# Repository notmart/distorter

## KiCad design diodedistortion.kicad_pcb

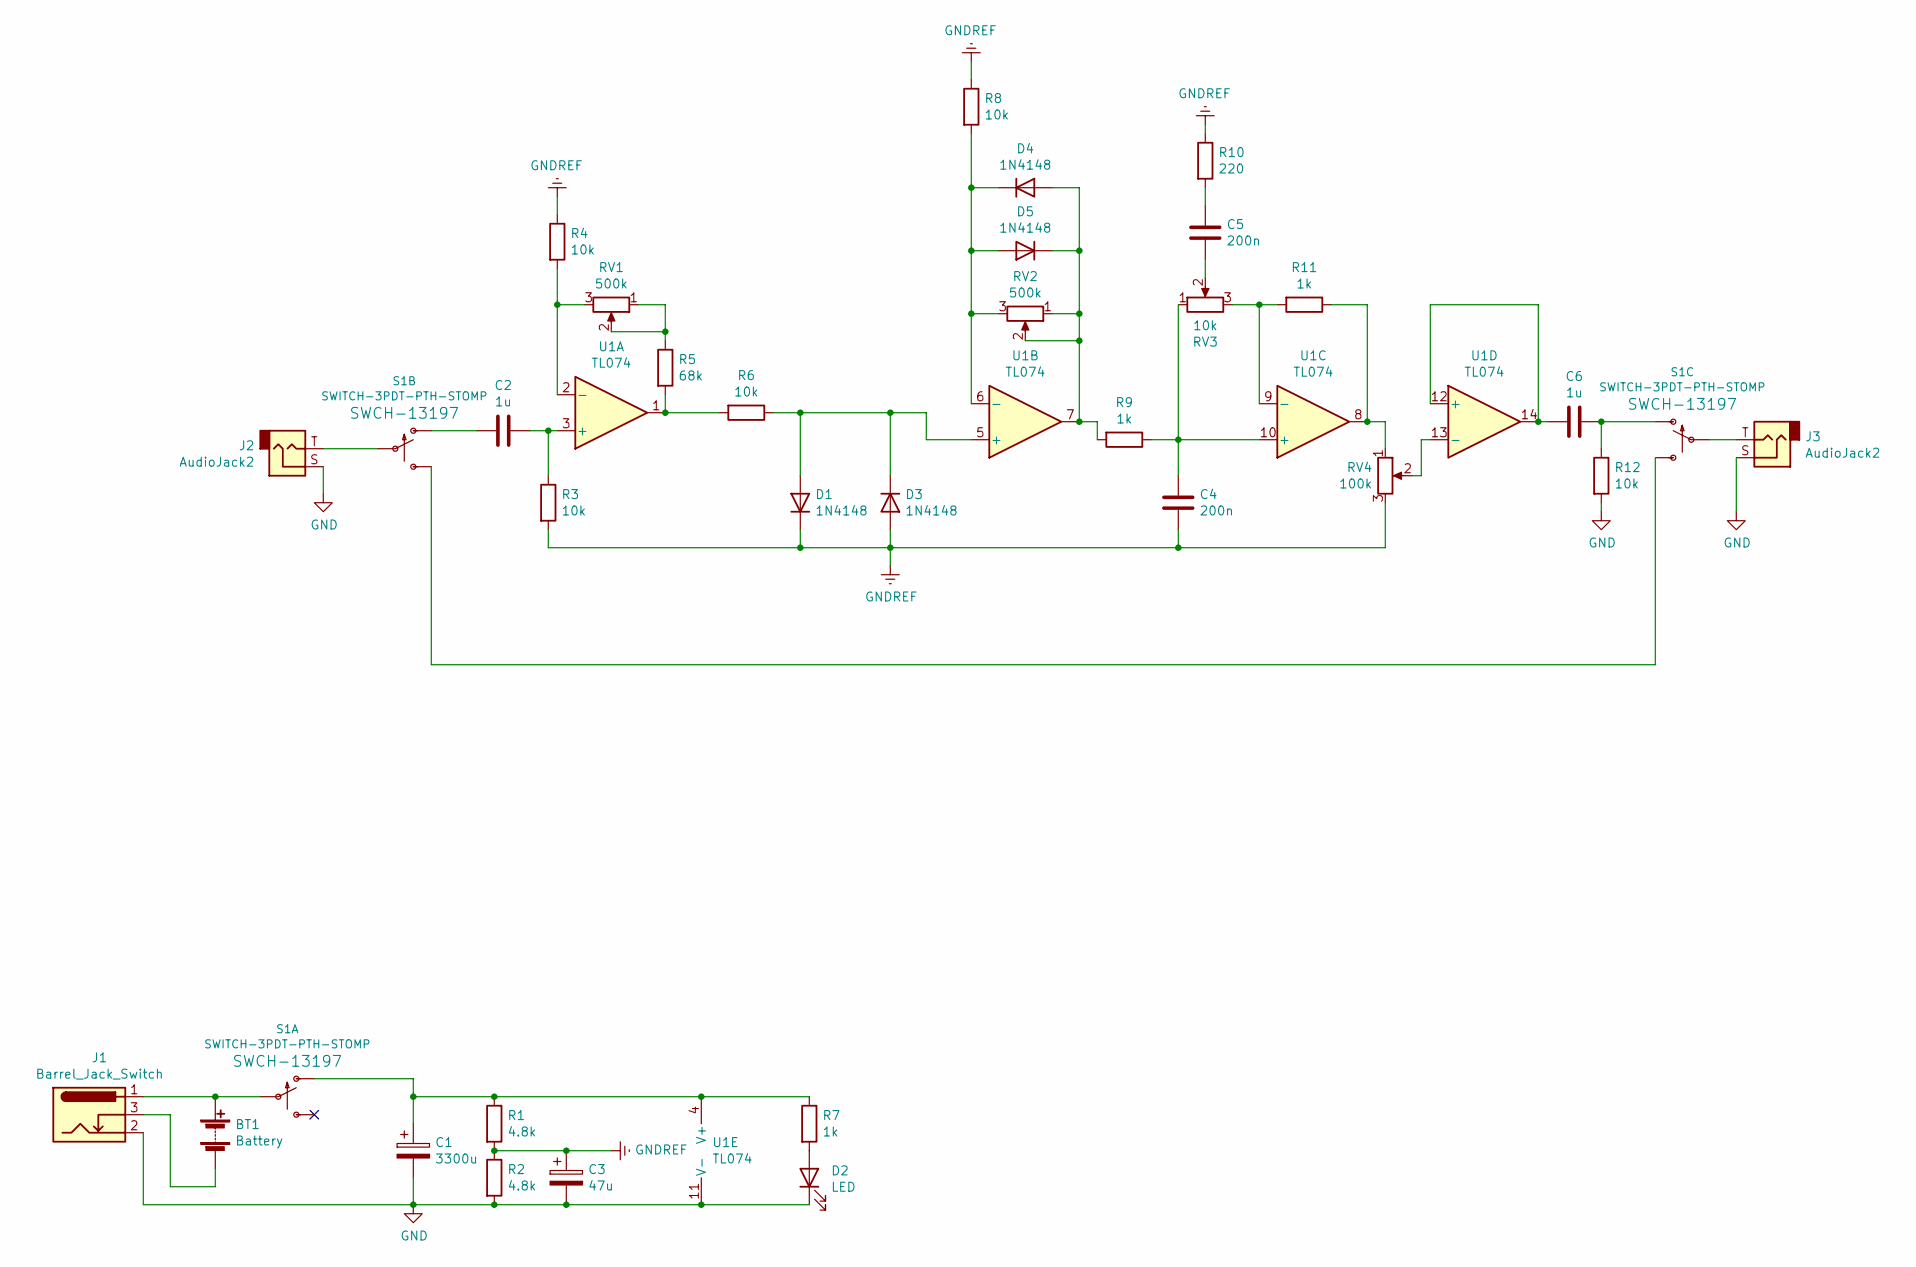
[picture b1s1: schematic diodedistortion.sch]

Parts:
BT1: Battery; 1X02
C1: 3300u; CP_Radial_D13.0mm_P5.00mm
C2, C6: 1u; C_Rect_L7.2mm_W2.5mm_P5.00mm_FKS2_FKP2_MKS2_MKP2
C3: 47u; CP_Radial_D8.0mm_P5.00mm
C4, C5: 200n; C_Rect_L7.2mm_W2.5mm_P5.00mm_FKS2_FKP2_MKS2_MKP2
D1, D3, D4, D5: 1N4148; D_DO-35_SOD27_P7.62mm_Horizontal
D2: LED; LED_D3.0mm
J1: Barrel_Jack_Switch; BarrelJack_Horizontal
J2, J3: AudioJack2; Jack 6.35mm PJ603
R1, R2: 4.8k; R_Axial_DIN0204_L3.6mm_D1.6mm_P7.62mm_Horizontal
R3, R4, R6, R8, R12: 10k; R_Axial_DIN0204_L3.6mm_D1.6mm_P7.62mm_Horizontal
R5: 68k; R_Axial_DIN0204_L3.6mm_D1.6mm_P7.62mm_Horizontal
R7, R9, R11: 1k; R_Axial_DIN0204_L3.6mm_D1.6mm_P7.62mm_Horizontal
R10: 220; R_Axial_DIN0204_L3.6mm_D1.6mm_P7.62mm_Horizontal
RV1, RV2: 500k; Potentiometer_Alps_RK09K_Single_Vertical
RV3: 10k; Potentiometer_Alps_RK09K_Single_Vertical
RV4: 100k; Potentiometer_Bourns_3386P_Vertical
S1: SWITCH-3PDT-PTH-STOMP; 3PDT_Small
U1: TL074; DIP-14_W7.62mm_Socket_LongPads

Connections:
GND: C1.2, C3.2, D2.1 (K), J1.2, J2.S, J3.S, R2.2, R12.2, U1.11 (V-)
GNDREF: C3.1, C4.2, D1.1 (K), D3.2 (A), R1.2, R2.1, R3.2, R4.1, R8.1, R10.1, RV4.3
unnamed: BT1.1 (+), J1.1, S1.P$2
unnamed: BT1.2 (-), J1.3
unnamed: C1.1, R1.1, R7.1, S1.P$1 (O), U1.4 (V+)
unnamed: C2.1, R3.1, U1.3 (+)
unnamed: C2.2, S1.P$4 (O)
unnamed: C4.1, R9.1, RV3.1, U1.10 (+)
unnamed: C5.1, R10.2
unnamed: C5.2, RV3.2
unnamed: C6.1, R12.1, S1.P$7 (O)
unnamed: C6.2, U1.12 (+), U1.14
unnamed: D1.2 (A), D3.1 (K), R6.1, U1.5 (+)
unnamed: D2.2 (A), R7.2
unnamed: D4.1 (K), D5.2 (A), R8.2, RV2.3, U1.6 (-)
unnamed: D4.2 (A), D5.1 (K), R9.2, RV2.1, RV2.2, U1.7
unnamed: J2.T, S1.P$5
unnamed: J3.T, S1.P$8
unnamed: R4.2, RV1.3, U1.2 (-)
unnamed: R5.1, RV1.1, RV1.2
unnamed: R5.2, R6.2, U1.1
unnamed: R11.1, RV4.1, U1.8
unnamed: R11.2, RV3.3, U1.9 (-)
unnamed: RV4.2, U1.13 (-)
unnamed: S1.P$6 (S), S1.P$9 (S)

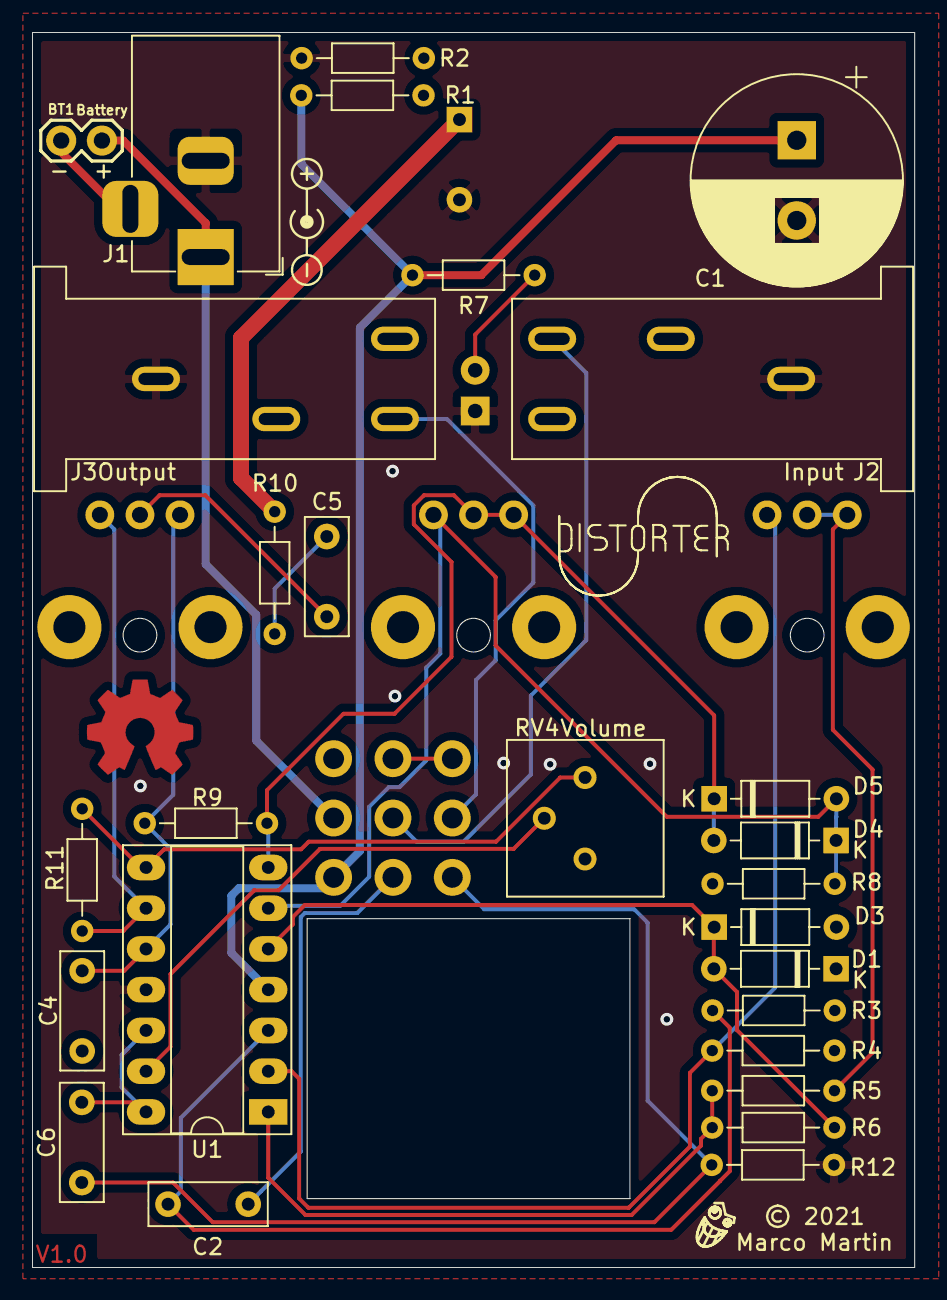
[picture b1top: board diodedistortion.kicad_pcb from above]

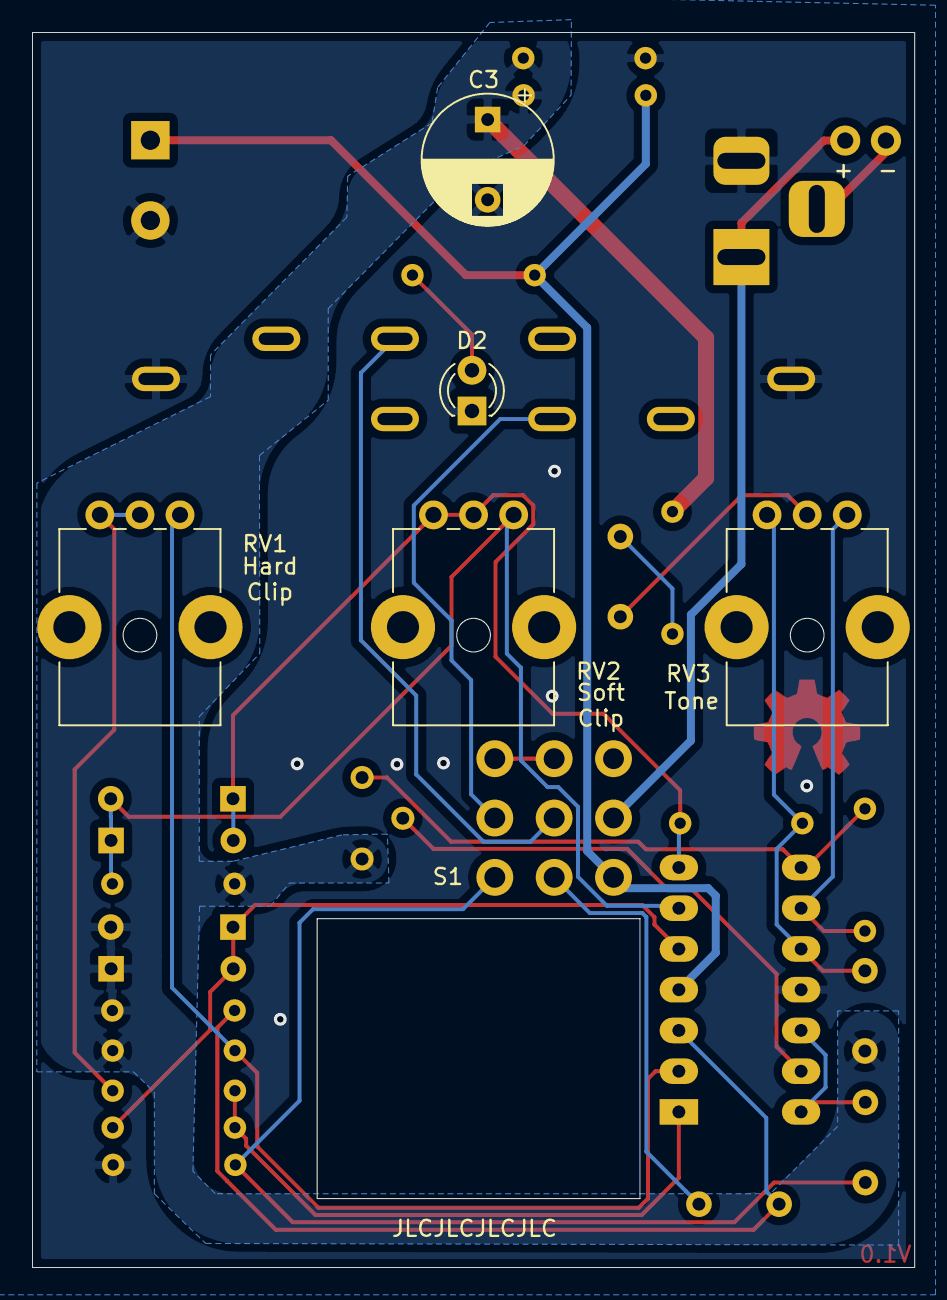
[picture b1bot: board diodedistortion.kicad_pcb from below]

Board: 2 copper layers, 55.0 x 77.0 mm, 33 parts (6 on the bottom side), 25 nets.

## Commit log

2021-12-06 nitial commit
2021-12-06 add license

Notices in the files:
diodedistortion.kicad_pcb:
© 2021
